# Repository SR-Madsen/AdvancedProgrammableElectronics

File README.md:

# Advanced Programmable Electronics
Repository used for storing projects from Vivado for the Advanced Programmable Electronics course on the 3rd semester of the Master in Electronics at the University of Southern Denmark.

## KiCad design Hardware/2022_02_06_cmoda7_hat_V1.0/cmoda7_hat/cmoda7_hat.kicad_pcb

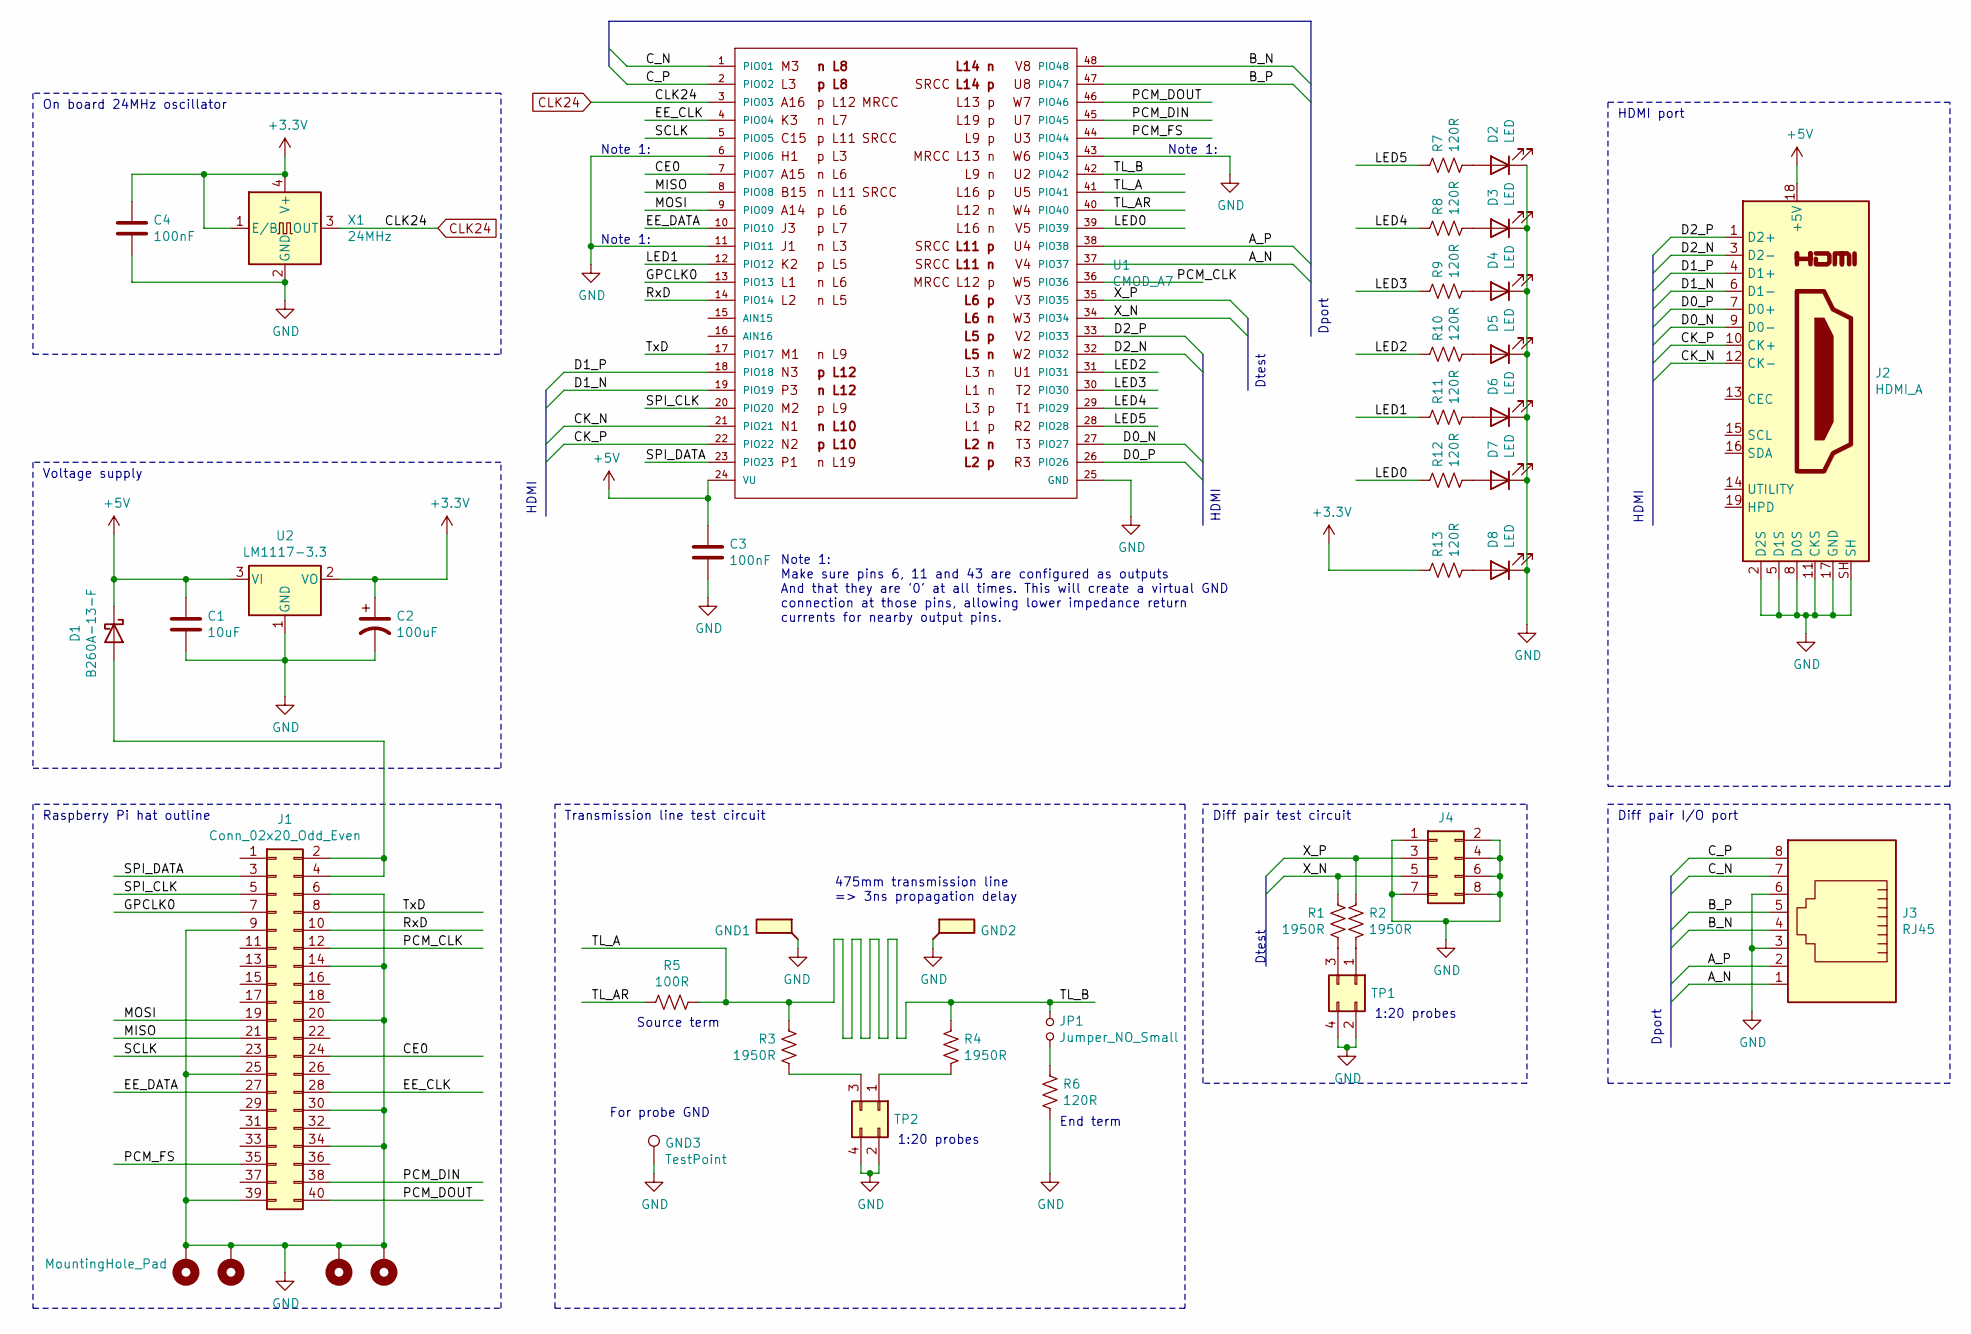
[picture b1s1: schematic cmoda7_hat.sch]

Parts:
C1: 10uF; C_1206_3216Metric_Pad1.33x1.80mm_HandSolder
C2: 100uF; CP_EIA-6032-20_AVX-F_Pad2.25x2.35mm_HandSolder
C3, C4: 100nF; C_1206_3216Metric_Pad1.33x1.80mm_HandSolder
D1: B260A-13-F; D_SMA_Handsoldering
D2, D3, D4, D5, D6, D7, D8: LED; LED_0805_2012Metric_Pad1.15x1.40mm_HandSolder
GND1, GND2: TestPoint_Flag; PROBE_PAD_1206
GND3: TestPoint; TestPoint_THTPad_2.0x2.0mm_Drill1.0mm
H1, H2, H3, H4: MountingHole_Pad; MountingHole_2.7mm_M2.5_DIN965_Pad
J1: Conn_02x20_Odd_Even; PinSocket_2x20_P2.54mm_Vertical
J2: HDMI_A; HDMI_A_Female_2000-1-2-41-00-BK
J3: RJ45; RJ45_Amphenol_54602-x08_Horizontal
J4: Conn_02x04_Odd_Even; PinHeader_2x04_P2.54mm_Horizontal
JP1: Jumper_NO_Small; SolderJumper-2_P1.3mm_Open_TrianglePad1.0x1.5mm
R1, R2, R3, R4: 1950R; R_1206_3216Metric_Pad1.30x1.75mm_HandSolder
R5: 100R; R_1206_3216Metric_Pad1.30x1.75mm_HandSolder
R6, R7, R8, R9, R10, R11, R12, R13: 120R; R_1206_3216Metric_Pad1.30x1.75mm_HandSolder
TP1, TP2: Conn_02x02_Odd_Even; PinHeader_2x02_P2.54mm_Vertical
U1: CMOD_A7
U2: LM1117-3.3; TO-252-2
X1: 24MHz; Oscillator_SMD_IQD_IQXO70-4Pin_7.5x5.0mm

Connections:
+3V3: C2.1, C4.1, R13.2, U2.2 (VO), X1.1 (E/B), X1.4 (V+)
+5V: C1.1, C3.1, D1.1 (K), J2.18 (+5V), U1.24 (VU), U2.3 (VI)
/A_N: J3.1, U1.37 (PIO37)
/A_P: J3.2, U1.38 (PIO38)
/B_N: J3.4, U1.48 (PIO48)
/B_P: J3.5, U1.47 (PIO47)
/CE0: J1.24, U1.7 (PIO07)
/CK_N: J2.12 (CK-), U1.21 (PIO21)
/CK_P: J2.10 (CK+), U1.22 (PIO22)
/C_N: J3.7, U1.1 (PIO01)
/C_P: J3.8, U1.2 (PIO02)
/D0_N: J2.9 (D0-), U1.27 (PIO27)
/D0_P: J2.7 (D0+), U1.26 (PIO26)
/D1_N: J2.6 (D1-), U1.19 (PIO19)
/D1_P: J2.4 (D1+), U1.18 (PIO18)
/D2_N: J2.3 (D2-), U1.32 (PIO32)
/D2_P: J2.1 (D2+), U1.33 (PIO33)
/EE_CLK: J1.28, U1.4 (PIO04)
/EE_DATA: J1.27, U1.10 (PIO10)
/GPCLK0: J1.7, U1.13 (PIO13)
/LED0: R12.2, U1.39 (PIO39)
/LED1: R11.2, U1.12 (PIO12)
/LED2: R10.2, U1.31 (PIO31)
/LED3: R9.2, U1.30 (PIO30)
/LED4: R8.2, U1.29 (PIO29)
/LED5: R7.2, U1.28 (PIO28)
/MISO: J1.21, U1.8 (PIO08)
/MOSI: J1.19, U1.9 (PIO09)
/PCM_CLK: J1.12, U1.36 (PIO36)
/PCM_DIN: J1.38, U1.45 (PIO45)
/PCM_DOUT: J1.40, U1.46 (PIO46)
/PCM_FS: J1.35, U1.44 (PIO44)
/RxD: J1.10, U1.14 (PIO14)
/SCLK: J1.23, U1.5 (PIO05)
/SPI_CLK: J1.5, U1.20 (PIO20)
/SPI_DATA: J1.3, U1.23 (PIO23)
/TL_A: JP1.1, R3.1, R4.1, R5.1, U1.41 (PIO41), U1.42 (PIO42)
/TL_AR: R5.2, U1.40 (PIO40)
/TxD: J1.8, U1.17 (PIO17)
/X_N: J4.5, R1.1, U1.34 (PIO34)
/X_P: J4.3, R2.1, U1.35 (PIO35)
CLK24: U1.3 (PIO03), X1.3 (OUT)
GND: C1.2, C2.2, C3.2, C4.2, D2.1 (K), D3.1 (K), D4.1 (K), D5.1 (K), D6.1 (K), D7.1 (K), D8.1 (K), GND1.1, GND2.1, GND3.1, H1.1, H2.1, H3.1, H4.1, J1.6, J1.9, J1.14, J1.20, J1.25, J1.30, J1.34, J1.39, J2.2 (D2S), J2.5 (D1S), J2.8 (D0S), J2.11 (CKS), J2.17 (GND), J2.SH, J3.3, J3.6, J4.1, J4.2, J4.4, J4.6, J4.7, J4.8, R6.1, TP1.2, TP1.4, TP2.2, TP2.4, U1.6 (PIO06), U1.11 (PIO11), U1.25 (GND), U1.43 (PIO43), U2.1 (GND), X1.2 (GND)
unnamed: D1.2 (A), J1.2, J1.4
unnamed: D2.2 (A), R7.1
unnamed: D3.2 (A), R8.1
unnamed: D4.2 (A), R9.1
unnamed: D5.2 (A), R10.1
unnamed: D6.2 (A), R11.1
unnamed: D7.2 (A), R12.1
unnamed: D8.2 (A), R13.1
unnamed: JP1.2, R6.2
unnamed: R1.2, TP1.3
unnamed: R2.2, TP1.1
unnamed: R3.2, TP2.3
unnamed: R4.2, TP2.1

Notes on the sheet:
Note 1:
Note 1: Make sure pins 6, 11 and 43 are configured as outputs And that they are '0' at all times. This will create a virtual GND connection at those pins, allowing lower impedance return currents for nearby output pins.
Raspberry Pi hat outline
Voltage supply
On board 24MHz oscillator
Source term
End term
1:20 probes
Transmission line test circuit
475mm transmission line => 3ns propagation delay
For probe GND
Diff pair test circuit
Diff pair I/O port
HDMI port
HDMI
Dtest
Dport

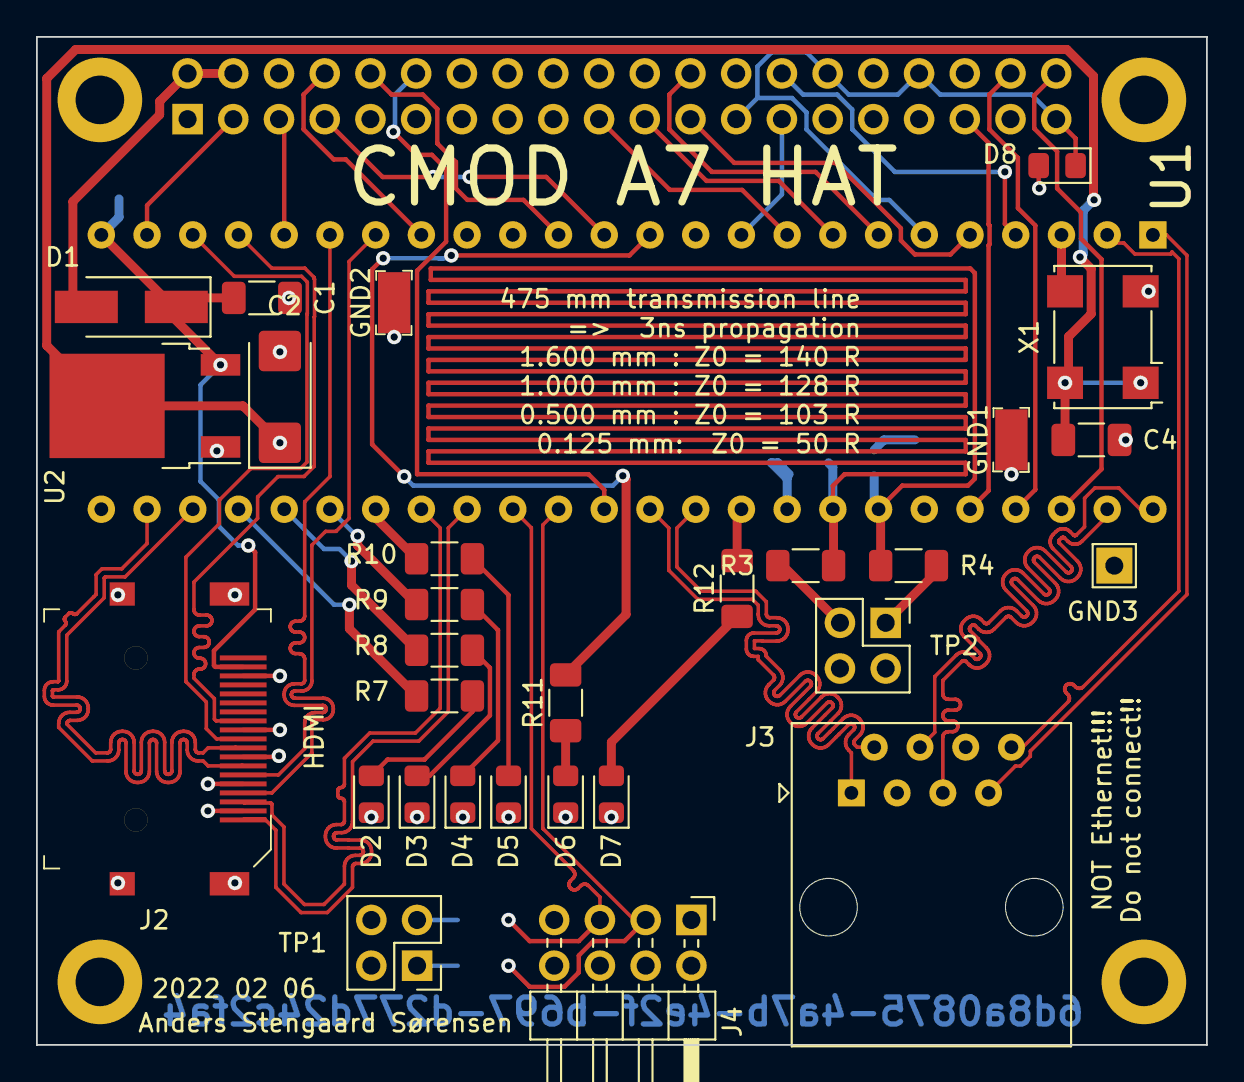
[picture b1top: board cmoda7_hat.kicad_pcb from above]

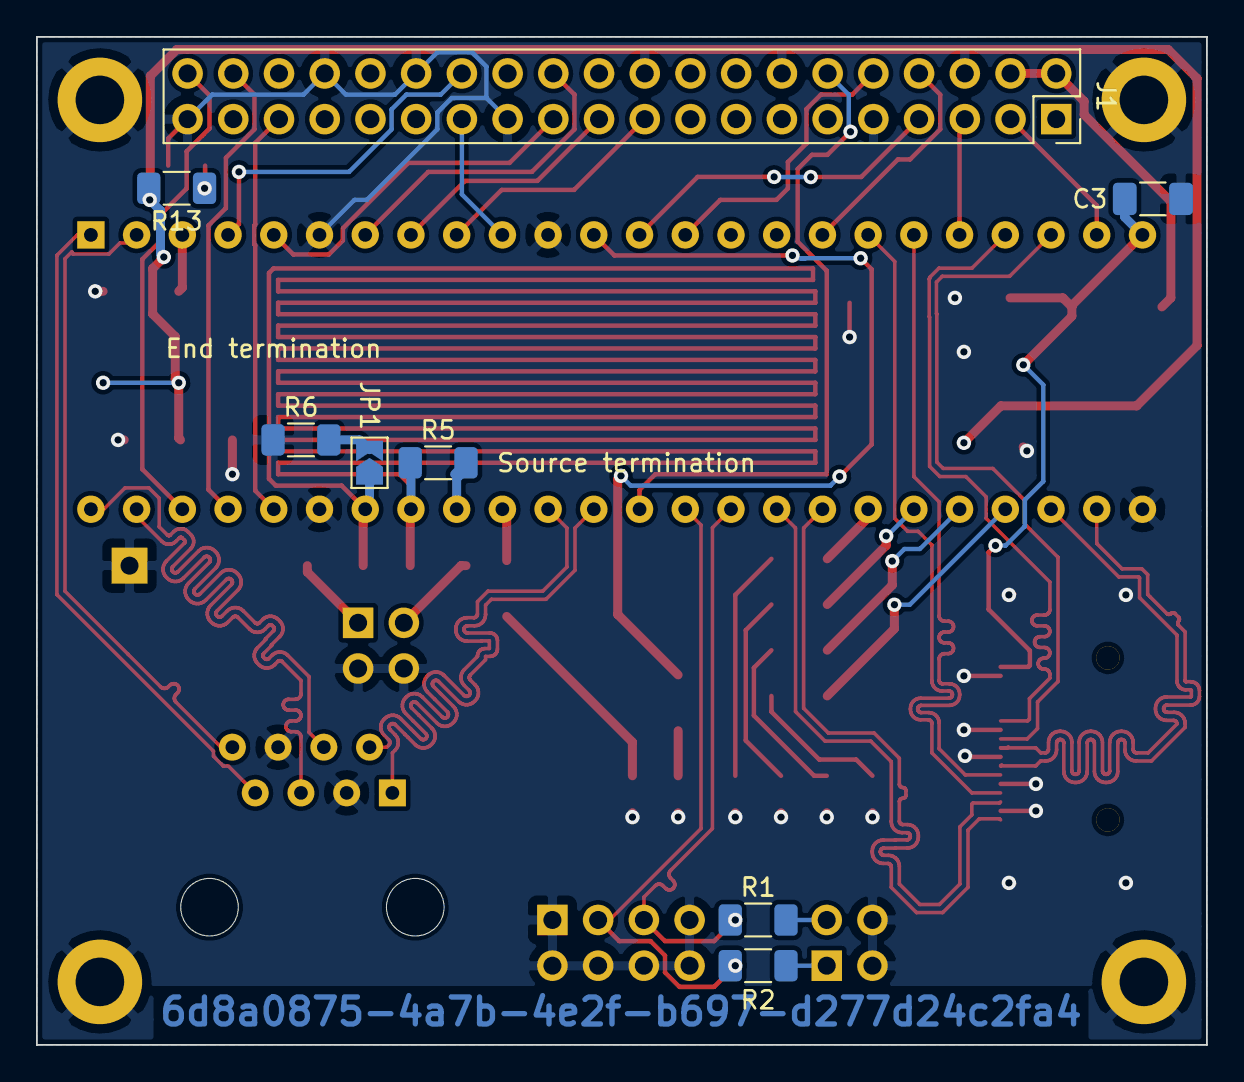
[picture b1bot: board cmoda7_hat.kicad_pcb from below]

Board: 2 copper layers, 65.0 x 56.0 mm, 42 parts (8 on the bottom side), 56 nets.

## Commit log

2022-02-04 Added first iteration of Lab 1.
2022-02-06 Added attempt at integrating inverters in VHDL, non-functional.
2022-02-14 Added some more from Lab 1.
2022-02-14 Added Lab 2 files (MMCM)
2022-02-21 Added Lab 3.
2022-03-02 Finished lab 3. Added lab 4 (UART) with functional TX and nearly finished RX.
2022-03-04 Made changes to UART RX, simulated but untested.
2022-03-04 Added tested UART RX module.
2022-03-14 Added functional Lab 5.
2022-03-15 Added attempted use of ILA for Lab 2 - bugged for unknown reasons.
2022-03-21 Finished Lab 6 based on QLink with added SPRAM.
2022-03-21 Added unfinished Rust serial communication program.
2022-03-22 Added finished Rust program for communication.
2022-03-23 Fixed Rust to correctly display returned string.
2022-03-23 Added fixed and tested Rust program.
2022-03-23 Added test of differential signal output buffer (I/O macro).
2022-03-28 Added HDMI driver files for Lab 7.
2022-03-29 Minor changes to Lab 6 and OBUFDS_Test. Ready for Lab 7 porting.
2022-03-31 Ported PLL to MMCM for Lab 7, optimized clock routing.
2022-04-05 Added OSERDES to HDMI sources, replacing shift register + DDR.
2022-04-06 Refactored to make clearer 'black boxes'. Prepared for 1080p.
2022-04-08 Upgraded HDMI transmitter to Full HD.
2022-04-11 Made custom box for display at 1920x1080@60Hz. Tested a bit.
2022-04-11 Small cleanup. Created memory configuration file. Untested due to hardware error.
2022-04-19 Fixed SERDES error due to not resetting correctly. Tested and fully functional for full HD.
2022-04-28 Created final project. Designed SPI module and connected to FIFO. Lacks many parts.
2022-05-03 Finished FIFO simulation, minor fixes implemented. Added pixel smoothening with DSP, lacks simulation.
2022-05-05 Fixed smoothening DSP from simulation. Started work on data controller.
2022-05-10 Finished data controller, simple simulation completed.
2022-05-17 Added board schematics. Further work on final project with simulation and bug fixing.
2022-05-23 Added SPI transfer Python script for Raspberry Pi.
2022-05-23 Fixed timing issues. Performed all simulations.
2022-05-24 Finished Python script, fixed minor VHDL errors and added ILA probes.
2022-05-26 Fixed SPI receiver final stage, added tri-state bidirectional to SRAM data.
2022-05-27 Minor changes to digital filter and data controller.
2022-05-27 Many minor changes to setup, few small fixes. Ironed out timing failures.
2022-05-28 Fixed something to make it work again, also changes to ILA setup. Added MCS file.
2022-05-28 Added attempt #1 at fixing digital filter. Simple, but unelegant.
2022-05-28 Added more elegant, robust solution for filter fix. Untested.
2022-05-29 Tested the elegant solution, works. Output from data controller is still incorrect.
2022-05-29 Improved Data Controller for better performance and robustness (#1)
    Added more elegant, robust solution for the Data Controller. Unfortunately did not fix issue with outputting current and next gamma values for digital filter.
2022-05-30 Implemented and simulated actual shift register for Data Controller. Untested on hardware.
